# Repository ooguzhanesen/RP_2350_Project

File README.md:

# RP2350 PALS OKUMA VE GONERME KARTI
## KART ÖZELLİKLERİ 
- RP2350 mikrodenetleyici
- MG2608 GSM Modülü
- Ds3231 RTC
- RS485
- 2 adet optoizalatörlü Pals okuma girişi
- Adc okuma girişi
- Type c girişi
- 7-28 to 5v voltaj girişi
- 5v multiplexer 

## PCB TASARIMI
PCB kiCad üzerinden 4 kartlı olacak şekilde tasarlanmıştır.

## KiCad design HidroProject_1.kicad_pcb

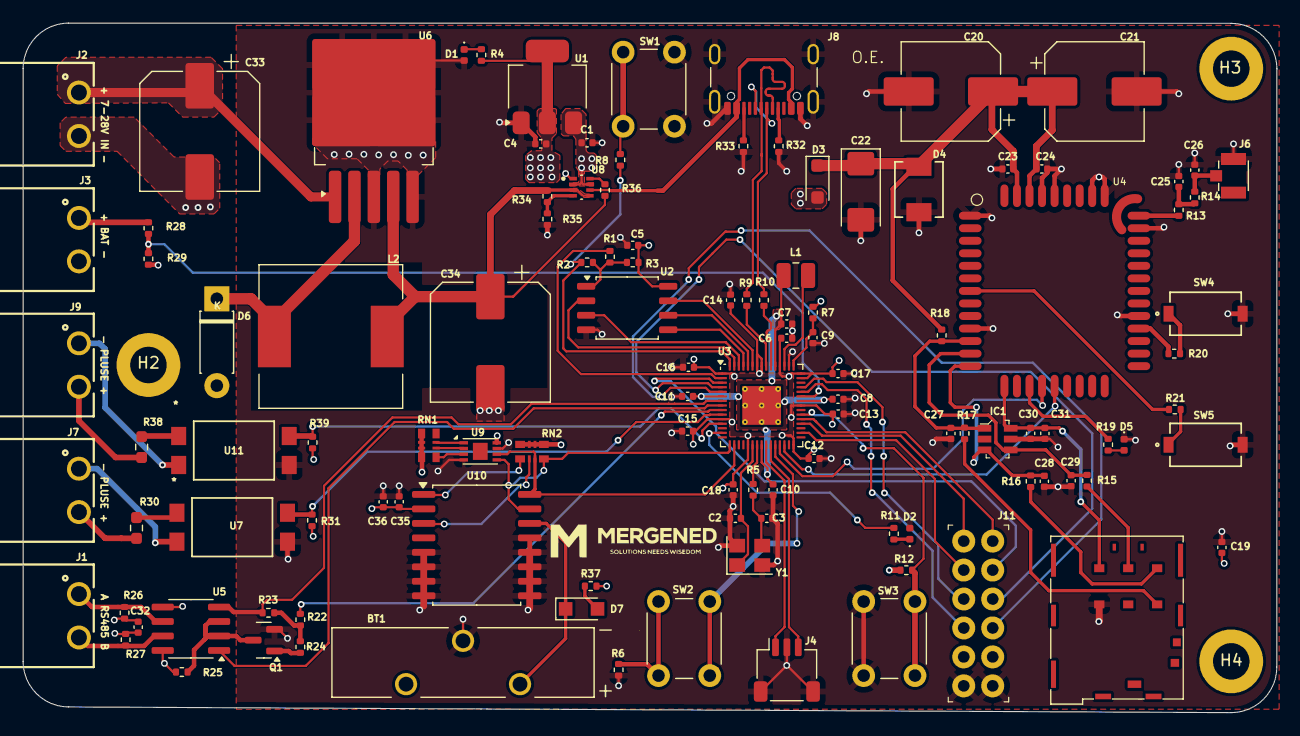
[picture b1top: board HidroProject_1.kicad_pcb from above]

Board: 4 copper layers, 110.0 x 60.5 mm, 119 parts (0 on the bottom side), 92 nets.

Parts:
BT1: 1074; BAT_1074
C1, C4, C19: 10u; C_0402_1005Metric
C2, C3: 15p; C_0402_1005Metric
C5, C8, C11, C12, C13, C14, C15, C16, C17, C18: 100n; C_0402_1005Metric
C6, C7, C9, C10: 4.7u; C_0402_1005Metric
C20: 100uF; CP_Elec_8x10.5
C21: 470uF; CP_Elec_8x10.5
C22: C_Small; CP_EIA-6032-15_Kemet-U
C23: 0.1uF; C_0402_1005Metric
C24, C27, C28, C29, C30: 33pF; C_0402_1005Metric
C25, C26: 10pF; C_0402_1005Metric
C31: 1uF; C_0402_1005Metric
C32: 100nF; C_0402_1005Metric
C33: 680uF; CP_Elec_10x10
C34: 220uF; CP_Elec_10x10
C35: 0.1u; C_0402_1005Metric
C36: 1u; C_0402_1005Metric
D1, D2: LG_L29K-G2J1-24-Z; D_0402_1005Metric
D3: D; D_SOD-123F
D4: D_Zener; SMB-2_4P60X3P95_ONS
D5: LED; LED_0402_1005Metric
D6: 1N5824; D_DO-41_SOD81_P7.62mm_Horizontal
D7: 1N4148; Nexperia_CFP3_SOD-123W
H2, H3, H4: MountingHole; MountingHole_3.2mm_M3_DIN965_Pad
IC1: DALC208SC6; SOT23-6L
J1, J2, J3, J7, J9: 691322310002
J4: SM03B-SRSS-TB; JST_SH_SM03B-SRSS-TB_1x03-1MP_P1.00mm_Horizontal
J5: JAE_SIM_Card_SF72S006
J6: U.FL-R-SMT-1_10_; HRS_U.FL-R-SMT-1_10_
J8: USB_C_Receptacle_USB2.0_16P; USB_C_Receptacle_GCT_USB4105-xx-A_16P_TopMnt_Horizontal
J11: 67996-412HLF; PinHeader_6x2_P2.54mm_Vertical
L1: 3.3u; L_1008_2520Metric
L2: 33uH; L_12x12mm_H8mm
Q1: BSN20; SOT-23
R1, R3: DNF; R_0402_1005Metric
R2, R13, R14, R22, R23: 0R; R_0402_1005Metric
R4, R5, R6, R8, R11: 1k; R_0402_1005Metric
R7: 33; R_0402_1005Metric
R9, R10: 27; R_0402_1005Metric
R12, R31, R34, R39: 10k; R_0402_1005Metric
R15, R16, R17: 22R; R_0402_1005Metric
R18: 15K; R_0402_1005Metric
R19, R20, R21, R29: 1K; R_0402_1005Metric
R24, R25, R26, R27: 10K; R_0402_1005Metric
R28: 5K; R_0402_1005Metric
R30, R38: R; R_0603_1608Metric_Pad0.98x0.95mm_HandSolder
R32, R33: 5k1; R_0402_1005Metric
R35: 3k; R_0402_1005Metric
R36: 4.7k; R_0402_1005Metric
R37: 220; R_0402_1005Metric
RN1, RN2: EXB28V472JX; C_ARRAY_EXB28V_PAN
SW1, SW2, SW3: SW_Push; SW_PUSH_6mm_H5mm
SW4, SW5: BTN_DEACTIVE; SW_PTS636_CNK
U1: NCP1117-3.3_SOT223; SOT-223-3_TabPin2
U2: W25Q128JVS; SOIC-8_5.23x5.23mm_P1.27mm
U3: RP2350_60QFN; QFN-60-1EP_7x7mm_P0.4mm_EP3.4x3.4mm_ThermalVias
U4: MG2608
U5: Max3075EESA; SOIC-8_3.9x4.9mm_P1.27mm
U6: LM2596S-5; TO-263-5_TabPin3
U7, U11: EL8171S1TU-G; EL8171-S1-TU_EVE
U8: TPS2117DRLR; SOTFL50P160X60-8N
U9: AT24CS01-MAHM; DFN-8-1EP_3x2mm_P0.5mm_EP1.3x1.5mm
U10: DS3231M; SOIC-16W_7.5x10.3mm_P1.27mm
Y1: ABM8-272-T3; Crystal_SMD_3225-4Pin_3.2x2.5mm

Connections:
32K: RN2.1, U10.1 (32KHZ)
+1V1: C7.1, C8.1, C10.1, C11.1, L1.1, U3.6 (DVDD), U3.23 (DVDD), U3.39 (DVDD), U3.50 (VREG_FB)
+3V3: C4.1, C5.1, C6.1, C12.1, C13.1, C14.1, C15.1, C16.1, C17.1, C18.1, C19.1, C32.1, C35.1, C36.1, J11.11, R3.1, R4.2, R7.1, R12.1, R25.1, R26.1, R31.1, R37.1, R39.1, RN1.5, RN1.6, RN1.7, RN1.8, RN2.5, RN2.6, RN2.7, RN2.8, U1.2 (VO), U2.8 (VCC), U3.1 (IOVDD), U3.11 (IOVDD), U3.20 (IOVDD), U3.30 (IOVDD), U3.38 (IOVDD), U3.44 (ADC_AVDD), U3.45 (IOVDD), U3.49 (VREG_VIN), U3.53 (USB_OTP_VDD), U3.54 (QSPI_IOVDD), U5.8 (VCC), U9.8 (VCC), U10.2 (VCC)
+5V: C1.1, D3.2 (A), J11.2, U1.3 (VI), U8.2 (VOUT), U8.7 (VOUT)
/28-5Regulator/5V_BAT: C34.1, L2.1, R34.1, R36.1, U6.4 (FB), U8.3 (VIN1), U8.5 (MODE)
/28-5Regulator/7-28v Input: C33.1, J2.1, U6.1 (VIN)
/ADC/ADC: R28.2, R29.1, U3.40 (GPIO26_ADC0)
/ADC/BAT+: J3.1, R28.1
/GPIO27: J11.10, U3.41 (GPIO27_ADC1)
/GPIO28: J11.9, U3.42 (GPIO28_ADC2)
/GSM_MODULE/4v: C20.1, C21.1, C22.1, C23.1, C24.1, D3.1 (K), D4.1 (K), R18.1, U4.42 (VBAT), U4.43 (VBAT)
/GSM_MODULE/Net_light: R19.1, U4.16 (NETL_LIGHT)
/GSM_MODULE/PWRKEY: R21.1, U4.7 (PWRKEY)
/GSM_MODULE/REST: R20.1, U4.26 (REST)
/GSM_MODULE/RF_ANT: R13.2, U4.35 (RF_ANT)
/GSM_MODULE/SIM_CLK: C28.1, IC1.3 (I/O_2), R16.2, U4.13 (SIM_CLK)
/GSM_MODULE/SIM_DATA: C27.1, IC1.1 (I/O_1), R17.2, R18.2, U4.11 (SIM_DATA)
/GSM_MODULE/SIM_RST: C29.1, IC1.4 (I/O_3), R15.2, U4.12 (SIM_RST)
/GSM_MODULE/SIM_VDD: C30.1, C31.1, IC1.6 (I/O_4), J5.C1 (VCC), U4.14 (SIM_VDD)
/GSM_MODULE/UART_RX: U3.27 (GPIO16), U4.17 (UART1_RXD)
/GSM_MODULE/UART_TX: U3.28 (GPIO17), U4.18 (UART1_TXD)
/I2C1_SCL: J11.3, U3.5 (GPIO3)
/I2C1_SDA: J11.4, U3.4 (GPIO2)
/RP-2350/1USB_D+: R9.2, U3.52 (USB_DP)
/RP-2350/1USB_D-: R10.2, U3.51 (USB_DM)
/RP-2350/FLASH_SS: R1.2, R2.2, R3.2, U2.1 (~CS)
/RP-2350/GPIO0: R1.1, U3.2 (GPIO0)
/RP-2350/GPIO2: R31.2, U3.10 (GPIO7), U7.4
/RP-2350/GPIO3: R39.2, U3.12 (GPIO8), U11.4
/RP-2350/QSPI_SCLK: U2.6 (CLK), U3.56 (QSPI_SCLK)
/RP-2350/QSPI_SD0: U2.5 (DI(IO0)), U3.57 (QSPI_SD0)
/RP-2350/QSPI_SD1: U2.2 (DO(IO1)), U3.59 (QSPI_SD1)
/RP-2350/QSPI_SD2: U2.3 (IO2), U3.58 (QSPI_SD2)
/RP-2350/QSPI_SD3: U2.7 (IO3), U3.55 (QSPI_SD3)
/RP-2350/QSPI_SS: R2.1, R8.1, U3.60 (QSPI_SS)
/RP-2350/RS485_EN: R22.1, U3.9 (GPIO6)
/RP-2350/RUN: SW2.2, U3.26 (RUN)
/RP-2350/SWCLK: J4.1, U3.24 (SWCLK)
/RP-2350/SWD: J4.3, U3.25 (SWD)
/RP-2350/UART_RX1: U3.8 (GPIO5), U5.1 (RO)
/RP-2350/UART_TX1: R23.1, U3.7 (GPIO4), U5.4 (DI)
/RP-2350/USB_D+: J8.A7 (D-), J8.B7 (D-), R9.1
/RP-2350/USB_D-: J8.A6 (D+), J8.B6 (D+), R10.1
/RP-2350/VREG_AVDD: C9.1, R7.2, U3.46 (VREG_AVDD)
/RP-2350/VREG_LX: L1.2, U3.48 (VREG_LX)
/RP-2350/XIN: C2.1, U3.21 (XIN), Y1.1
/RP-2350/XOUT: R5.1, U3.22 (XOUT)
/RP-2350/~USB_BOOT: R8.2, SW1.2
/RS485/RS485_A: J1.1, R26.2, U5.6 (A)
/RS485/RS485_B: J1.2, R27.1, U5.7 (B)
/SPI0_CS: J11.5, U3.3 (GPIO1)
/SPI0_MISO: J11.8, U3.32 (GPIO20)
/SPI0_MOSI: J11.6, U3.35 (GPIO23)
/SPI0_SCK: J11.7, U3.34 (GPIO22)
/USB_TYPE_C/5V_USB: J8.A4 (VBUS), J8.A9 (VBUS), J8.B4 (VBUS), J8.B9 (VBUS), U8.6 (VIN2)
GND: BT1.N, C1.2, C2.2, C3.2, C4.2, C5.2, C6.2, C7.2, C8.2, C9.2, C10.2, C11.2, C12.2, C13.2, C14.2, C15.2, C16.2, C17.2, C18.2, C19.2, C20.2, C21.2, C22.2, C23.2, C24.2, C25.2, C26.2, C27.2, C28.2, C29.2, C30.2, C31.2, C32.2, C33.2, C34.2, C35.2, C36.2, D1.2, D2.2, D4.2 (A), D5.1 (K), D6.2 (A), IC1.5 (REF_1), J2.2, J3.2, J4.2, J4.MP (MountPin), J5.C5 (GND), J6.1, J8.A1 (GND), J8.A12 (GND), J8.B1 (GND), J8.B12 (GND), J8.S1 (SHIELD), J11.1, J11.12, Q1.2 (S), R6.2, R27.2, R29.2, R32.2, R33.2, R35.2, SW1.1, SW3.1, SW4.2, SW5.2, U1.1 (GND), U2.4 (GND), U3.47 (VREG_PGND), U3.61 (GND), U4.1 (GND), U4.10 (GND), U4.27 (GND), U4.34 (GND), U4.36 (GND), U4.37 (GND), U4.40 (GND), U4.41 (GND), U5.5 (GND), U6.3 (GND), U6.5 (~ON/OFF), U7.3, U8.1 (GND), U9.4 (GND), U9.7 (WP), U10.5 (GND), U10.6 (GND), U10.7 (GND), U10.8 (GND), U10.9 (GND), U10.10 (GND), U10.11 (GND), U10.12 (GND), U10.13 (GND), U11.3, Y1.2, Y1.4
unnamed: C3.1, R5.2, Y1.3
unnamed: C25.1, R13.1, R14.2
unnamed: C26.1, J6.2, R14.1
unnamed: D1.1, R4.1
unnamed: D2.1, R11.1
unnamed: D5.2 (A), R19.2
unnamed: D6.1 (K), L2.2, U6.2 (OUT)
unnamed: D7.2 (A), R37.2
unnamed: BT1.P_1, D7.1 (K), U10.14 (VBAT)
unnamed: J5.C3 (CLK), R16.1
unnamed: J5.C7 (I/O), R17.1
unnamed: J5.C2 (RST), R15.1
unnamed: J7.1, U7.2
unnamed: J7.2, R30.1
unnamed: J8.A5 (CC1), R32.1
unnamed: J8.B5 (CC2), R33.1
unnamed: J9.1, U11.2
unnamed: J9.2, R38.1
unnamed: Q1.3 (D), R25.2, U5.2 (~RE), U5.3 (DE)
unnamed: Q1.1 (G), R24.2
unnamed: R6.1, SW2.1
unnamed: R20.2, SW4.1
unnamed: R21.2, SW5.1
unnamed: R22.2, R23.2, R24.1
unnamed: R30.2, U7.1
unnamed: R38.2, U11.1
unnamed: R11.2, U3.14 (GPIO10)
unnamed: R12.2, SW3.2, U3.36 (GPIO24)
unnamed: R34.2, R35.1, U8.4 (PR1)
unnamed: R36.2, U8.8 (ST)
unnamed: RN1.3, U9.1 (A0)
unnamed: RN1.2, U9.2 (A1)
unnamed: RN1.1, U9.3 (A2)
SCL: RN2.3, U3.17 (GPIO13), U9.6 (SCL), U10.16 (SCL)
SDA: RN2.4, U3.16 (GPIO12), U9.5 (SDA), U10.15 (SDA)
SQW: RN2.2, U10.3 (~INT/SQW)

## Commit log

2025-01-04 fist commit
2025-01-04 mahlas guncellendi
